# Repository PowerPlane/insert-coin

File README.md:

# Ducky Card

> An interactive business card that comes to life when you insert a CR2032 coin cell.
> Inspired by the Target gift cards of the early 2000s.

The card is a PCB cut to business-card size. The coin cell is the interaction: slide it into the holder and the card boots, blinks, listens for a blow, writes a fortune to its NFC tag, then sleeps. Tap it with a phone and the fortune opens in the pond, a small web app where the ducks you collect live.

This repo is one card project: the board, its firmware and its pond. Collaborations live in their own repos, started from this one (see [Collabs](#collabs)).

## Layout

```
ducky-card/
├── README.md
├── COLLABS.md             how to start a collab repo from this one
├── hardware/              one KiCad project per board revision, each with production/
├── firmware/              PlatformIO project (bringup, production,
│   │                      production-nfc, production-pond envs)
│   └── lib/card-identity/ card serial, signing and NFC record, shared with pond/
├── enclosure/             3D-printed sleeves and holders
├── tools/                 build-hex.sh and its test
├── pond/                  web app on Vercel, including the /flash page
└── docs/                  board notes, flasher, NFC, pond docs
```

## The board

Business card size (about 85 × 54 mm), ATtiny1616, 24 LEDs, a MEMS microphone and an ST25DV04K NFC tag. Details in [`docs/board.md`](docs/board.md).

- ATtiny1616: [datasheet](https://ww1.microchip.com/downloads/en/DeviceDoc/ATtiny1614-16-17-DataSheet-DS40002204A.pdf)
- ST25DV04K: [datasheet](https://www.st.com/resource/en/datasheet/st25dv04k.pdf)

`hardware/` holds one folder per board revision (V0-1, V0-2, V0-3); open the `.kicad_pro` inside one in KiCad 10. The revision table is in [`docs/board.md`](docs/board.md#hardware-files).

## Build and flash

[PlatformIO](https://platformio.org/) + [megaTinyCore](https://github.com/SpenceKonde/megaTinyCore), flashed over UPDI. Wiring, environments and build commands are in [`firmware/README.md`](firmware/README.md).

```bash
cd firmware && pio run -e production-pond
```

`production-pond` needs `firmware/production-pond/src/secrets.h` (copy `secrets.h.example`); its key must match the pond's `CARD_SECRET`. It is gitignored and never committed.

**Coming from the old layout** (`variants/business-card-v1/`)? git moves tracked files but not ignored ones, so after pulling, move your key and card list yourself. Do not make a new key: cards flashed with it would never verify against the live pond.

```bash
mv variants/business-card-v1/firmware/production-pond/src/secrets.h firmware/production-pond/src/secrets.h
```

```bash
mv variants/business-card-v1/cards.csv cards.csv
```

No PlatformIO on the machine? [`tools/build-hex.sh`](tools/build-hex.sh) builds a `.hex` to send, and [`ducky.davidyang.work/flash`](docs/flasher/README.md) flashes it from a browser through an Adafruit UPDI Friend.

## The pond

`pond/` is deployed to [ducky.davidyang.work](https://ducky.davidyang.work) on Vercel, backed by Turso. Hosting: [`docs/pond/HOSTING.md`](docs/pond/HOSTING.md). Everything else about the pond: [`docs/pond/README.md`](docs/pond/README.md).

```bash
cd pond && npm ci && npm run verify
```

## Collabs

A collab is a separate repo made from this one with GitHub's "Use this template", with its own pond, its own NFC host and its own card secret. Steps: [`COLLABS.md`](COLLABS.md).

| Repo | Pond |
|---|---|
| `PowerPlane/ducky-card` (this one) | Shared pond |
| [`Dav1dyang/ducky-card-spencer-collab`](https://github.com/Dav1dyang/ducky-card-spencer-collab) | Personal pond, with Spencer Chang |

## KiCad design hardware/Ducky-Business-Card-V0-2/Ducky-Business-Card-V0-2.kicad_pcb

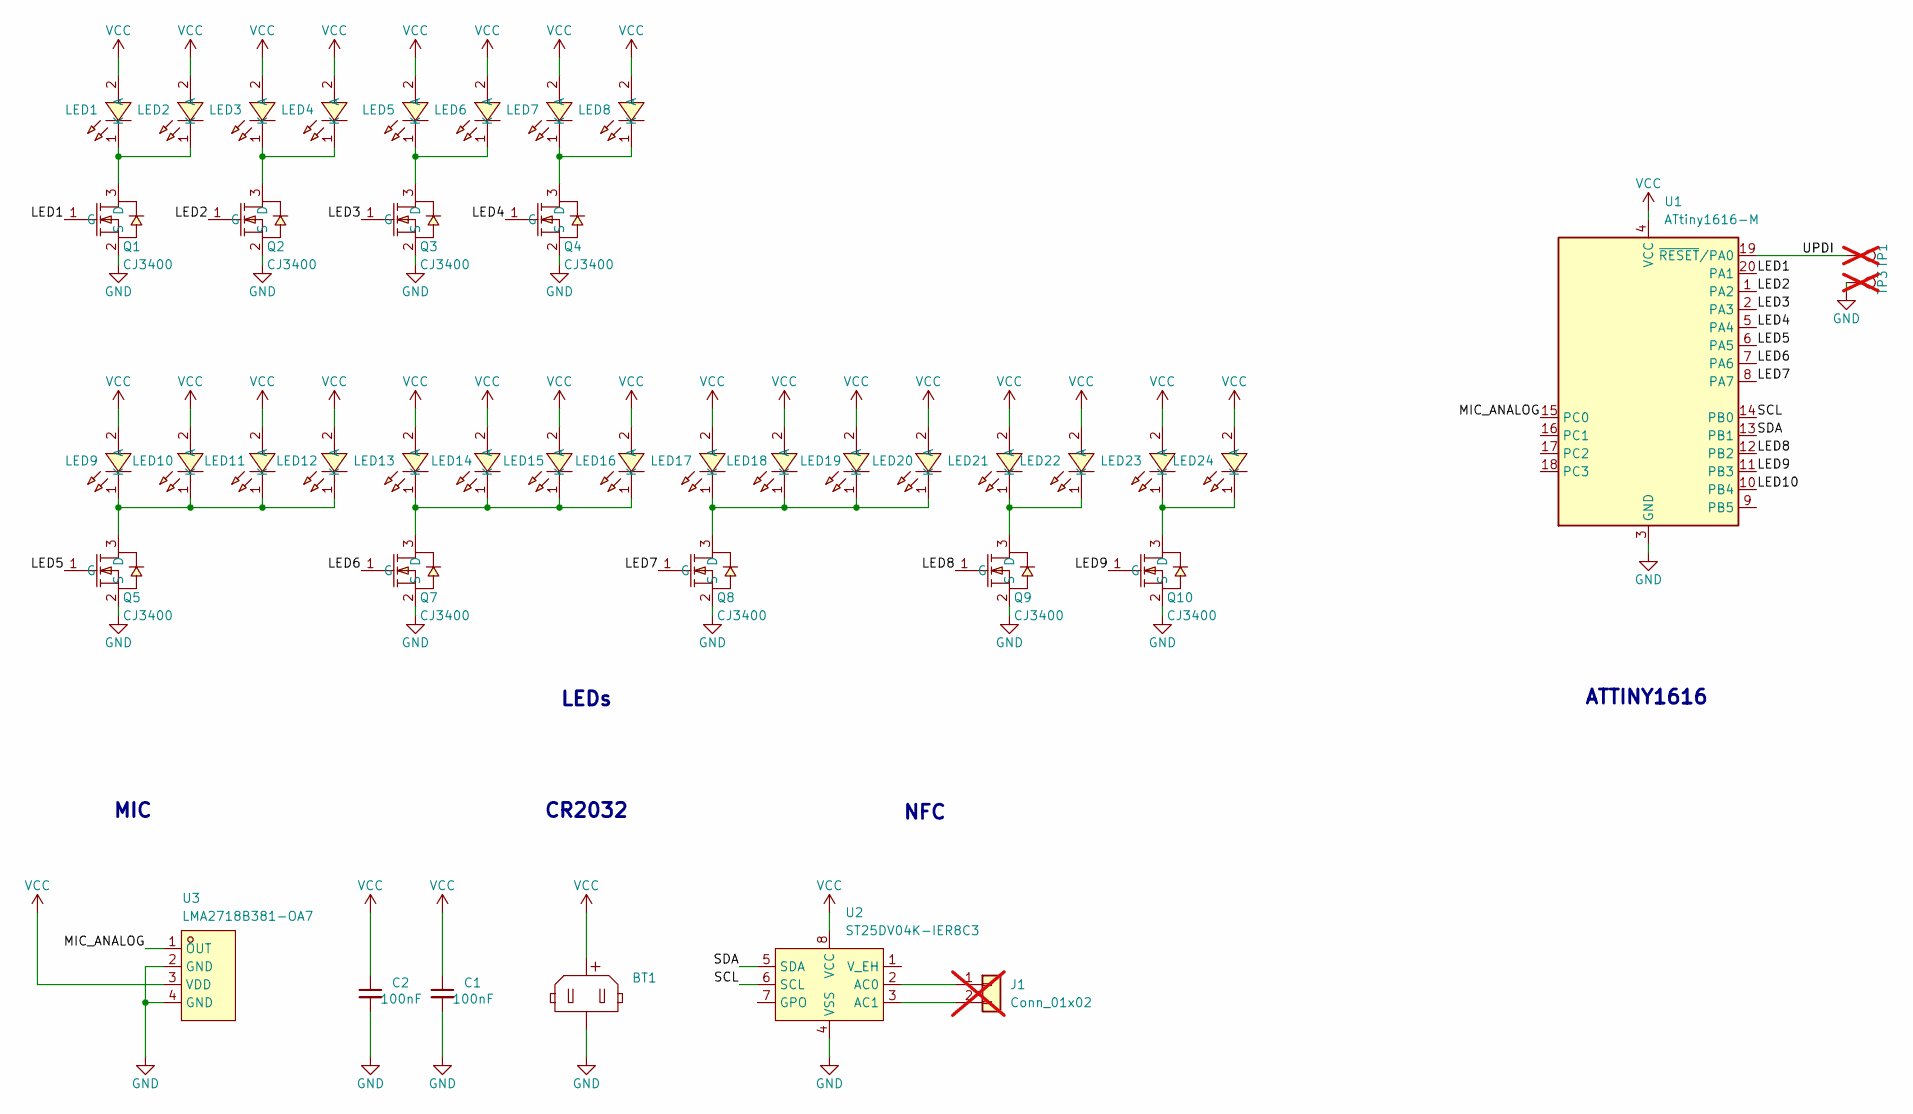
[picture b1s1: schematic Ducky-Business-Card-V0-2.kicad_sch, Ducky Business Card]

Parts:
BT1: Battery-Holder_Coin-Cell_CR2032_Linx_BAT-HLD-001; BAT-SMD_MY-2032-08
C1, C2: 100nF; C_0805; Voltage 50V; Tolerance 100%; LCSC C28233
J1: Conn_01x02; NFC_Mini_Antenna_22x22_ST25DV04K; not fitted
LED1, LED2, LED3, LED4, LED5, LED6, LED7, LED8, LED9, LED10, LED11, LED12, LED13, LED14, LED15, LED16, LED17, LED18, LED19, LED20: XL-1606UYC; LED-SMD_L1.7-W1.1-RD_RED-SIDE; MPN XL-1606SURC; LCSC C965862
LED21, LED22: XL-1606UOC; LED-SMD_L1.7-W1.1-RD_RED-SIDE; MPN XL-1606SURC; LCSC C965860
LED23, LED24: XL-1606SURC; LED-SMD_L1.7-W1.1-RD_RED-SIDE; MPN XL-1606SURC; LCSC C965861
Q1, Q2, Q3, Q4, Q5, Q7, Q8, Q9, Q10: CJ3400; SOT23-3; MPN CJ3400; LCSC C19019
TP1, TP3: 1.0mm; DUCKY_ICON_2.54_Spacing; not fitted
U1: ATtiny1616-M; VQFN-20-1EP_3x3mm_P0.4mm_EP1.7x1.7mm; LCSC C507118
U2: ST25DV04K-IER8C3; DFN-8-1EP_3x2mm_P0.5mm_EP1.36x1.46mm; LCSC C5221756
U3: LMA2718B381-OA7; MIC-SMD_4P-L2.8-W1.9_LMA2718B381-OA7; MPN LMA2718B381-OA7; LCSC Part C5373222

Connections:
/LED1: Q1.1 (G), U1.20 (PA1)
/LED2: Q2.1 (G), U1.1 (PA2)
/LED3: Q3.1 (G), U1.2 (PA3)
/LED4: Q4.1 (G), U1.5 (PA4)
/LED5: Q5.1 (G), U1.6 (PA5)
/LED6: Q7.1 (G), U1.7 (PA6)
/LED7: Q8.1 (G), U1.8 (PA7)
/LED8: Q9.1 (G), U1.12 (PB2)
/LED9: Q10.1 (G), U1.11 (PB3)
/LED10: U1.10 (PB4)
/MIC_ANALOG: U1.15 (PC0), U3.1 (OUT)
/SCL: U1.14 (PB0), U2.6 (SCL)
/SDA: U1.13 (PB1), U2.5 (SDA)
/UPDI: TP1.1 (1_1), U1.19 (~RESET/PA0)
GND: BT1.2 (-), C1.2, C2.2, Q1.2 (S), Q2.2 (S), Q3.2 (S), Q4.2 (S), Q5.2 (S), Q7.2 (S), Q8.2 (S), Q9.2 (S), Q10.2 (S), TP3.1 (1_1), U1.3 (GND), U1.21 (GND), U2.4 (VSS), U3.2 (GND), U3.4 (GND)
unnamed: J1.1, U2.2 (AC0)
unnamed: J1.2, U2.3 (AC1)
unnamed: LED1.1 (K), LED2.1 (K), Q1.3 (D)
unnamed: LED3.1 (K), LED4.1 (K), Q2.3 (D)
unnamed: LED5.1 (K), LED6.1 (K), Q3.3 (D)
unnamed: LED7.1 (K), LED8.1 (K), Q4.3 (D)
unnamed: LED9.1 (K), LED10.1 (K), LED11.1 (K), LED12.1 (K), Q5.3 (D)
unnamed: LED13.1 (K), LED14.1 (K), LED15.1 (K), LED16.1 (K), Q7.3 (D)
unnamed: LED17.1 (K), LED18.1 (K), LED19.1 (K), LED20.1 (K), Q8.3 (D)
unnamed: LED21.1 (K), LED22.1 (K), Q9.3 (D)
unnamed: LED23.1 (K), LED24.1 (K), Q10.3 (D)
VCC: BT1.1 (+), C1.1, C2.1, LED1.2 (A), LED2.2 (A), LED3.2 (A), LED4.2 (A), LED5.2 (A), LED6.2 (A), LED7.2 (A), LED8.2 (A), LED9.2 (A), LED10.2 (A), LED11.2 (A), LED12.2 (A), LED13.2 (A), LED14.2 (A), LED15.2 (A), LED16.2 (A), LED17.2 (A), LED18.2 (A), LED19.2 (A), LED20.2 (A), LED21.2 (A), LED22.2 (A), LED23.2 (A), LED24.2 (A), U1.4 (VCC), U2.8 (VCC), U3.3 (VDD)

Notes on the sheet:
NFC
LEDs
CR2032
ATTINY1616
MIC

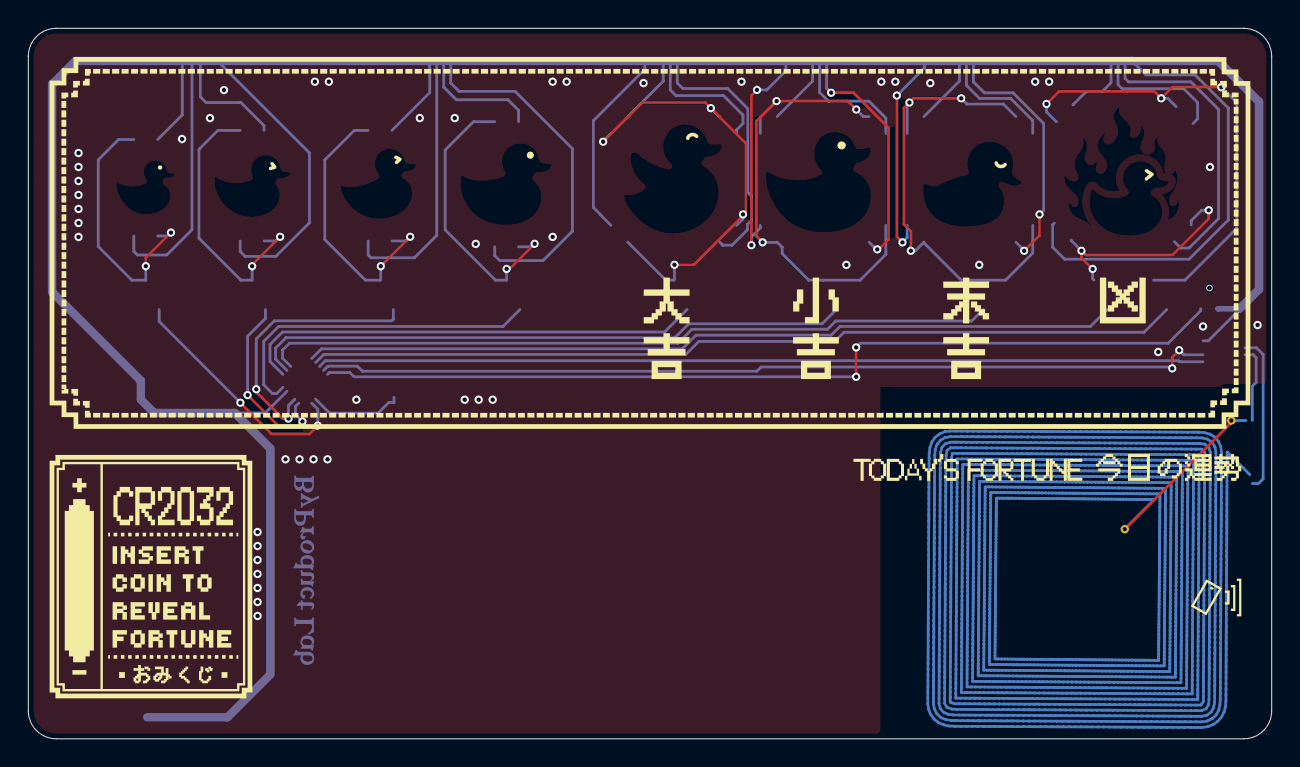
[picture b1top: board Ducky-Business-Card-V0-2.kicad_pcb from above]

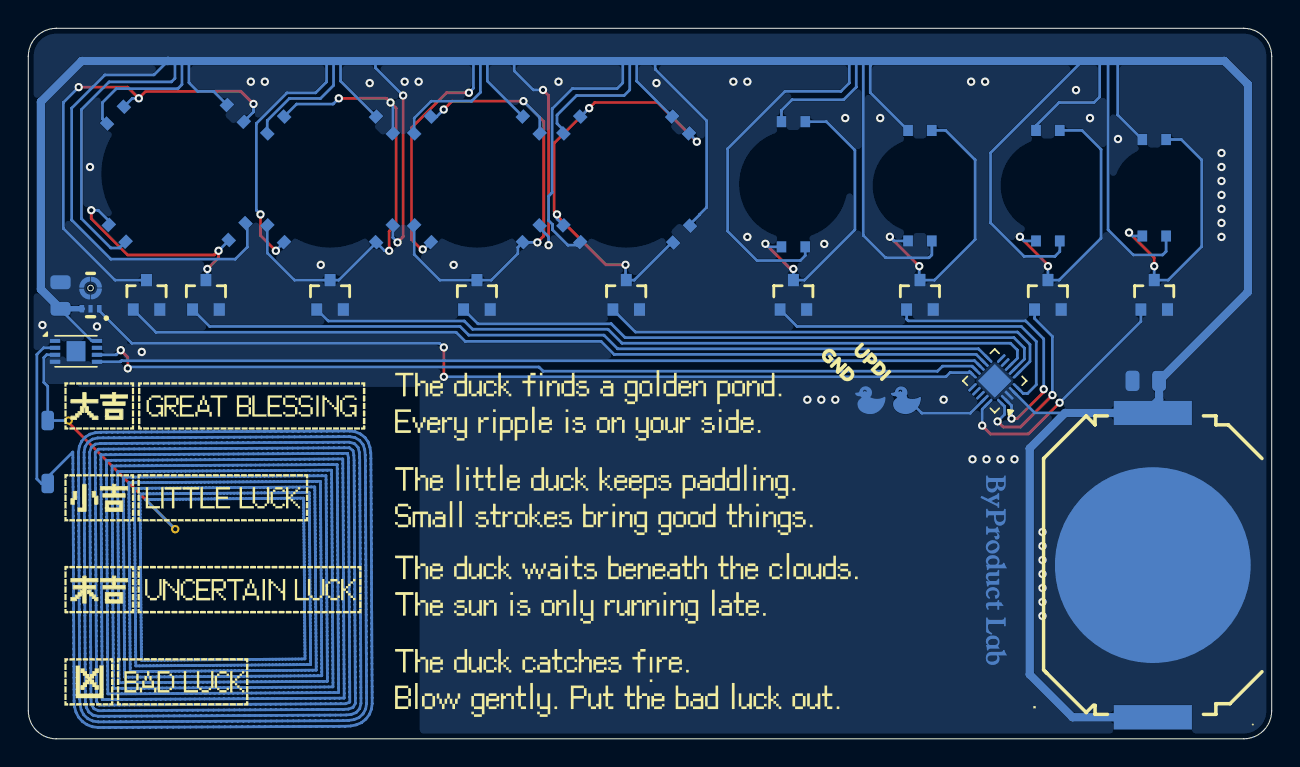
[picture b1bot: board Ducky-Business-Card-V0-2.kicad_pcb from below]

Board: 2 copper layers, 88.9 x 50.8 mm, 44 parts (44 on the bottom side), 26 nets.

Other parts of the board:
kibuzzard-6A02DFFE: G***; kibuzzard-6A02DFFE
kibuzzard-6A02E019: G***; kibuzzard-6A02E019

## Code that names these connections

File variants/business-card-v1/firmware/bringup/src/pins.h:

// Pin map for business-card-v1 (ATtiny1616 VQFN-20).
// Verified against hardware/production/netlist.ipc — do not edit without
// re-checking the netlist.
//
// TODO: extract to insert-coin/shared/firmware/ when production firmware
// is written and a second consumer exists.

#pragma once

#include <Arduino.h>

#define NUM_BANKS 9

// LED cathode-bank gate drivers (active high; gate HIGH -> bank lit).
// Each "bank" sinks the cathodes of a fixed group of LEDs to GND.
//
//   Bank 0  PA1  D1, D2          (Q1)
//   Bank 1  PA2  D3, D4          (Q2)
//   Bank 2  PA3  D5, D6          (Q3)
//   Bank 3  PA4  D7, D8          (Q4)
//   Bank 4  PA5  D9, D10, D11, D12   (Q5)
//   Bank 5  PA6  D13, D14, D15, D16  (Q7)
//   Bank 6  PA7  D17, D18, D19, D20  (Q8)
//   Bank 7  PB2  D21, D22        (Q9)
//   Bank 8  PB3  D23, D24        (Q10)
//
// Individual-LED addressing is not possible: all 24 anodes go through
// individual current-limit resistors to VCC, so an LED is lit whenever
// its bank's MOSFET is on.
constexpr uint8_t LED_BANK_PINS[NUM_BANKS] = {
    PIN_PA1, PIN_PA2, PIN_PA3, PIN_PA4, PIN_PA5,
    PIN_PA6, PIN_PA7, PIN_PB2, PIN_PB3,
};

// Microphone analog input.
// On the ATtiny1616 txy6 pin map, PC0 is ADC1 AIN6 -- NOT ADC0 AIN6
// (ADC0 AIN6 is PA6, which is LED bank 5). Sampling ADC0 here would
// read the LED gate, not the mic.
#define MIC_PIN          PIN_PC0
#define MIC_ADC          ADC1
#define MIC_ADC_MUXPOS   ADC_MUXPOS_AIN6_gc

// I2C bus to ST25DV04K NFC tag (default TWI pins).
//   PB0 = SCL
//   PB1 = SDA
// The PCB has no external pull-ups; firmware enables the ATtiny's
// internal pull-ups before Wire.begin().
#define ST25DV_I2C_ADDR_USER   0x53  // 7-bit, user EEPROM
#define ST25DV_I2C_ADDR_SYSTEM 0x57  // 7-bit, system config area

// Pins broken out from the MCU but not wired to anything on the PCB.
// Disable their input buffers to keep sleep leakage down.
//   PB4 -- /LED10 net stub: out of MCU but nothing on the other end
//   PB5 -- no connect
//   PC1, PC2, PC3 -- no connect
constexpr uint8_t UNUSED_PINS[] = {
    PIN_PB4, PIN_PB5, PIN_PC1, PIN_PC2, PIN_PC3,
};
constexpr uint8_t NUM_UNUSED_PINS = sizeof(UNUSED_PINS) / sizeof(UNUSED_PINS[0]);

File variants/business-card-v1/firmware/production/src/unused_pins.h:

// Disable the digital input buffer on every pin the PCB doesn't use.
// Critical for sleep current: a floating input buffer can leak
// 1-10 uA per pin, dominating the < 1 uA sleep target.

#pragma once

#include <Arduino.h>

#include "pins.h"

// megaTinyCore exposes getPINnCTRLregister() returning a volatile uint8_t*
// to the PINnCTRL register for the given Arduino pin.
inline void configure_unused_pins() {
    for (uint8_t i = 0; i < NUM_UNUSED_PINS; i++) {
        volatile uint8_t* pinctrl = getPINnCTRLregister(
            digitalPinToPortStruct(UNUSED_PINS[i]),
            digitalPinToBitPosition(UNUSED_PINS[i]));
        if (pinctrl) {
            *pinctrl = PORT_ISC_INPUT_DISABLE_gc;
        }
    }
    // Production never touches I2C -- the ST25DV04K NFC tag is RF-
    // powered for tap-to-URL independent of the MCU. PB0/PB1 have no
    // external pull-ups, so their input buffers would float during the
    // whole show without this.
    PORTB.PIN0CTRL = PORT_ISC_INPUT_DISABLE_gc;
    PORTB.PIN1CTRL = PORT_ISC_INPUT_DISABLE_gc;
    // PA0 = UPDI -- owned by hardware, leave alone.
    // PC0 = mic -- input buffer needed for the ADC.
}

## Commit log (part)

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2026-05-18 default to production & Kicad Resistor fix
2026-05-20 update kicad notes
2026-05-20 NFC ducky: post-reveal URL patch + Cargo.site snippet
    Adds a side-by-side production-nfc firmware variant (sibling to
    production) that writes the fortune result to the ST25DV04K NDEF
    EEPROM over I2C after the reveal animation. A pre-programmed URL
    of the form https://davidyang.work/?d=0 is patched in a single byte
    at offset 0x001D to encode the fortune (1..4), then reset to 0 after
    NDEF_EXPIRY_SECONDS so the next visitor lands on the plain page.
2026-05-20 Address codex review: deinit mic before NFC sleep, fix README env
    - main.cpp: unconditionally mic_deinit() after anim_run_reveal() so
    bad-luck activations don't keep ADC1 (~25 uA) enabled through the
    60 s URL-live sleep.
    - production-nfc/README.md: replace "pio run -e production" with
    "-e production-nfc" so following the doc actually builds the NFC
    variant.
2026-05-20 Address /review: refresh stale I2C comments in NFC variant
    unused_pins.h and sleepy.cpp were carrying over the original
    production/ rationale that "the show never touches I2C." That's
    no longer true in production-nfc -- ndef_init() flips PB0/PB1
    between input-disable and pullup+TWI across the run. Code was
    already correct (input-disable still runs at the right moments);
    just rewriting the comments so the next reader doesn't get
2026-05-20 NFC: patch URL before reveal so taps during show see new fortune
    Previously the I2C write to the ST25DV happened after anim_run_reveal()
    returned, so a phone tap during the 12-15 s LED show still read the
    previous fortune's URL. Moving the patch to right after the lottery
    decision means the URL is live ~11 ms after the fortune is picked --
    visually instantaneous, before the first reveal LED ramps.
    The write is ~11 ms blocking (3 ms TWI @ 25 kHz + 6 ms EEPROM cycle),
2026-05-21 PCB File Updated
    - updated the pcb layout and mic choice to have it be economy parts for jlc.
    - removed the VCC testpoint
    - change UPDI & GND testpoint to be ducky shape
